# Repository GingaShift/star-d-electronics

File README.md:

# STAR-D Electronics

Electronics repository for the STAR-D (Space Test of Amoeba Response - Dictyostelium) experiment developed within the ESA REXUS/BEXUS programme.

The electronics architecture is divided into several dedicated boards responsible for power conversion, experiment control, imaging, sensing, actuation and illumination.

---

# System Overview

The STAR-D electronics system is organized around:

- Power Board
- Main Control Board
- 5V Distribution Board
- CM5 Imaging System
- Microscope LED Board
- External Sensor Interfaces

---

# Power Board

## Purpose

Interfaces directly with the REXUS Service Module.

Responsibilities:

- 28V input from REXUS
- Power conversion
- Signal isolation
- RS422 communications
- Power distribution to the experiment

## PCB

## Main Components

- DC/DC Converters
- Optocouplers
- RS422 Transceiver
- D-SUB Interface
- Protection circuitry

---

# Main Control Board

## Purpose

Central controller of the experiment.

Responsibilities:

- Sensor acquisition
- Heater control
- Fluidic control
- Experiment sequencing
- Telemetry generation

## PCB

## Main Components

- ESP32-S3
- MAX31865
- PT100 Interface
- LSM6DSM
- ABP Pressure Sensor Interface
- SLF3S Flow Sensor Interface
- Actuator Drivers

---

# 5V Distribution Board

## Purpose

Dedicated power distribution board for high-current 5V subsystems.

Responsibilities:

- CM5 power supply

## PCB

---

# CM5 Imaging System

## Purpose

Scientific image acquisition and storage.

Responsibilities:

- Microscope control
- Camera acquisition
- Data storage
- Image processing

## PCB

## Main Components

- Raspberry Pi CM5
- NVMe SSD
- CSI Camera Interface

---

# Microscope LED PCB

## Purpose

Microscope illumination.

Responsibilities:

- Brightfield illumination
- Fluorescence illumination

## PCB

---

# External BME280 Board

## Purpose

Environmental monitoring outside the Pressure Vessel.

## PCB

---

# Repository Structure

```text
Documentation/
├── SED
├── Part_Listing
├── ICD
└── Images

Power_Board/

Main_Board/

5V_Board/

CM5_System/

Microscope_LED_PCB/

BME280_External/
```

---

# Documentation

Useful documents:

- STAR-D SED
- REXUS ICD
- Global Part Listing
- Power Board Part Listing
- Test Reports
- Integration Documents

---

# Team

STAR-D Electronics Team

Electronic Lead:
**Eden Elfassy**

ESA REXUS/BEXUS Programme

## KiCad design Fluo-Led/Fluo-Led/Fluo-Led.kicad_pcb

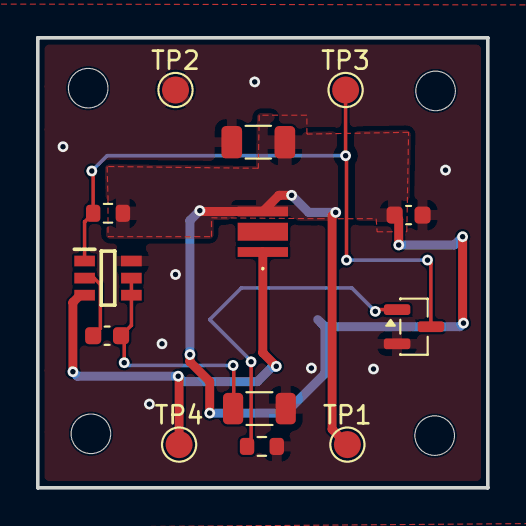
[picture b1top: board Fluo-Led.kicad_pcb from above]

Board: 2 copper layers, 25.0 x 25.0 mm, 18 parts (1 on the bottom side), 7 nets.

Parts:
C1: 100nF 0603; C_0603_1608Metric
C2: 10uF 1206; C_1206_3216Metric
C3: 1 nF 0603; C_0603_1608Metric
H1, H2, H3, H4: MountingHole; MountingHole_2.2mm_M2
IC1: AL5801W6-7; SOT95P285X140-6N
J1: Conn_01x03; Molex_Micro-Fit_3.0_43650-0312_1x03-1MP_P3.00mm_Horizontal
LED1: LV_CRBP.01-KXLY-AD-Q525-350-R18; LVCRBP01KXLYADQ525350R18
Q1: 2N7002; SOT-23
R1: 4.02R 1206; R_1206_3216Metric
R2: 12.4k 0603; R_0603_1608Metric
R3: 100k 0603; R_0603_1608Metric
TP1, TP2, TP3, TP4: TestPoint; TestPoint_Pad_D1.5mm

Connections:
+5V: C1.1, C2.1, J1.1, LED1.2 (A), R2.1, TP1.1 (1_1)
BIAS: IC1.1 (BIAS), Q1.3 (D), R2.2, TP3.1 (1_1)
GND: C1.2, C2.2, IC1.6 (GND), J1.2, Q1.2 (S), R1.2, R3.1, TP2.1 (1_1)
unnamed: C3.1, IC1.4 (REXT), IC1.5 (COMP), R1.1
unnamed: C3.2, IC1.2 (FB)
unnamed: IC1.3 (OUT), LED1.1 (K), TP4.1 (1_1)
PWM_CTRL: J1.3, Q1.1 (G), R3.2

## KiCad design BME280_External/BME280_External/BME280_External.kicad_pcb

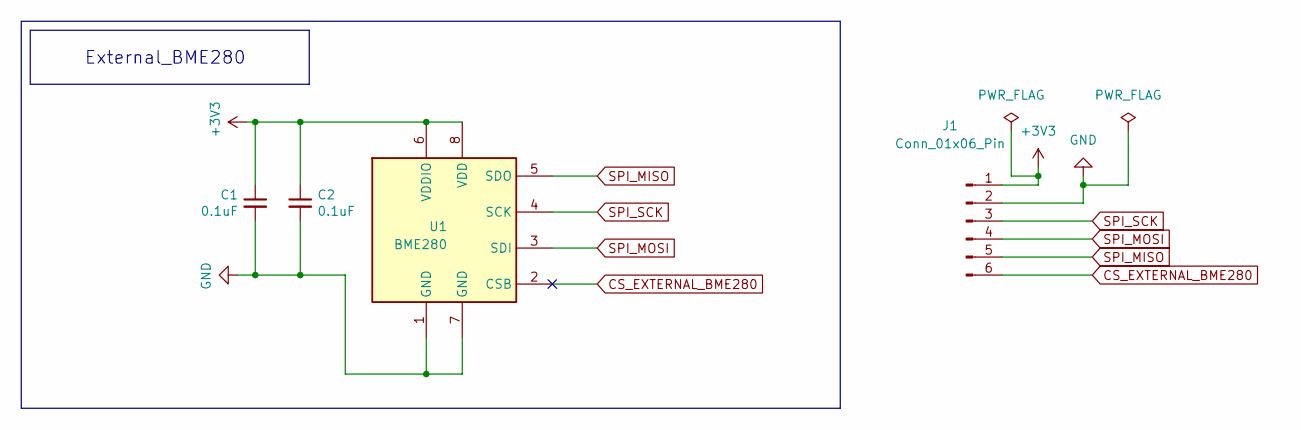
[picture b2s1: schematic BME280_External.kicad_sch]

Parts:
C1, C2: 0.1uF; C_0402_1005Metric
J1: Conn_01x06_Pin; Molex_Micro-Fit_3.0_43650-0615_1x06_P3.00mm_Vertical
U1: BME280; Bosch_LGA-8_2.5x2.5mm_P0.65mm_ClockwisePinNumbering

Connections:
+3V3: C1.1, C2.1, J1.1, U1.6 (VDDIO), U1.8 (VDD)
CS_EXTERNAL_BME280: J1.6, U1.2 (CSB)
GND: C1.2, C2.2, J1.2, U1.1 (GND), U1.7 (GND)
SPI_MISO: J1.5, U1.5 (SDO)
SPI_MOSI: J1.4, U1.3 (SDI)
SPI_SCK: J1.3, U1.4 (SCK)

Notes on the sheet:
External_BME280

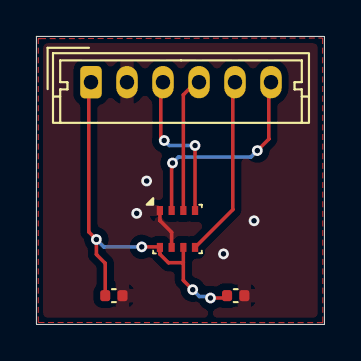
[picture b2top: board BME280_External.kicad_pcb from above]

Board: 2 copper layers, 16.0 x 16.0 mm, 4 parts (0 on the bottom side), 6 nets.

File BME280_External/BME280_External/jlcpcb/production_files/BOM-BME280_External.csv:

Comment,Designator,Footprint,LCSC,Quantity
0.1uF,"C1,C2",C_0402_1005Metric,C141382,2
BME280,U1,Bosch_LGA-8_2.5x2.5mm_P0.65mm_ClockwisePinNumbering,C92489,1
Conn_01x06_Pin,J1,Molex_Micro-Latch_53253-0670_1x06_P2.00mm_Vertical,C564034,1

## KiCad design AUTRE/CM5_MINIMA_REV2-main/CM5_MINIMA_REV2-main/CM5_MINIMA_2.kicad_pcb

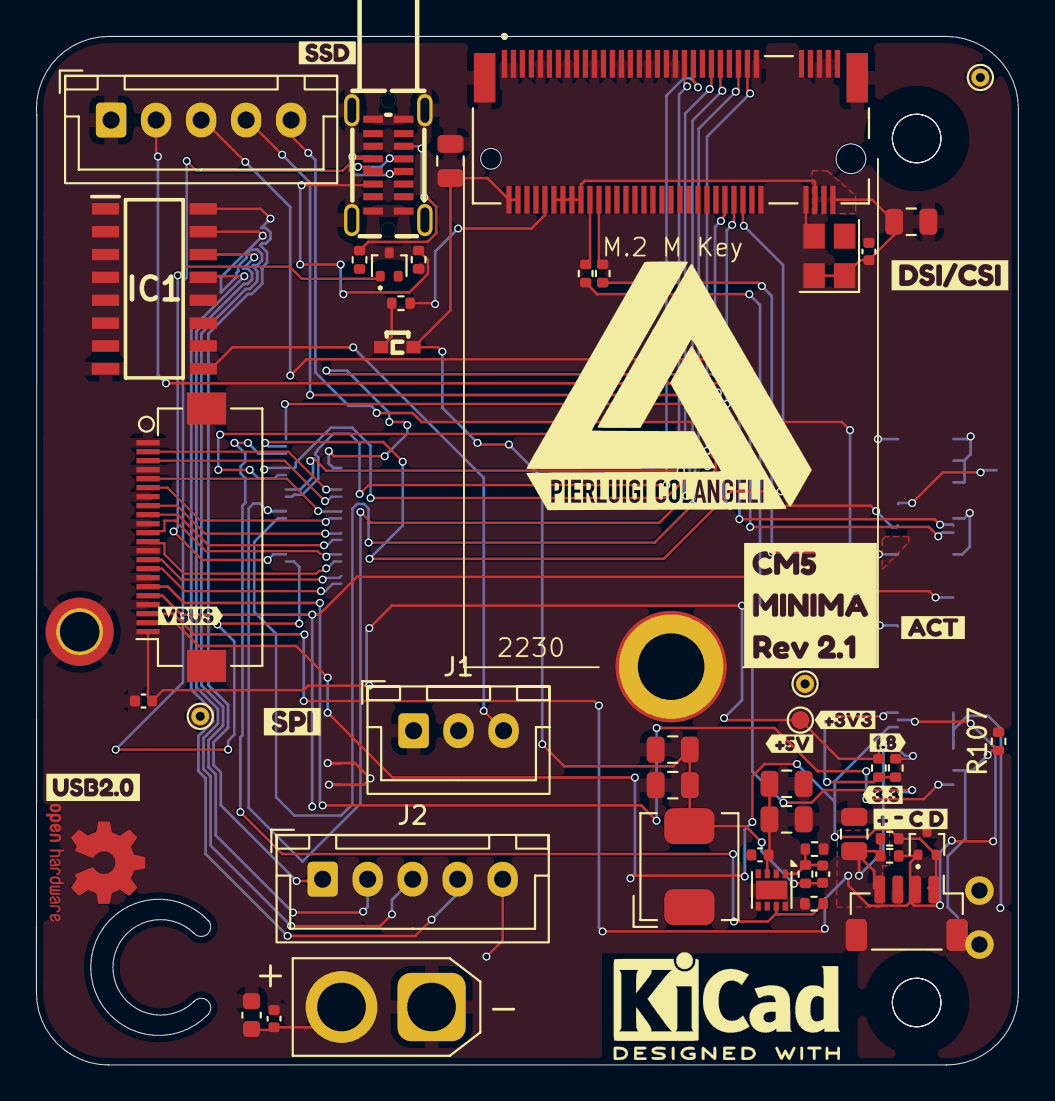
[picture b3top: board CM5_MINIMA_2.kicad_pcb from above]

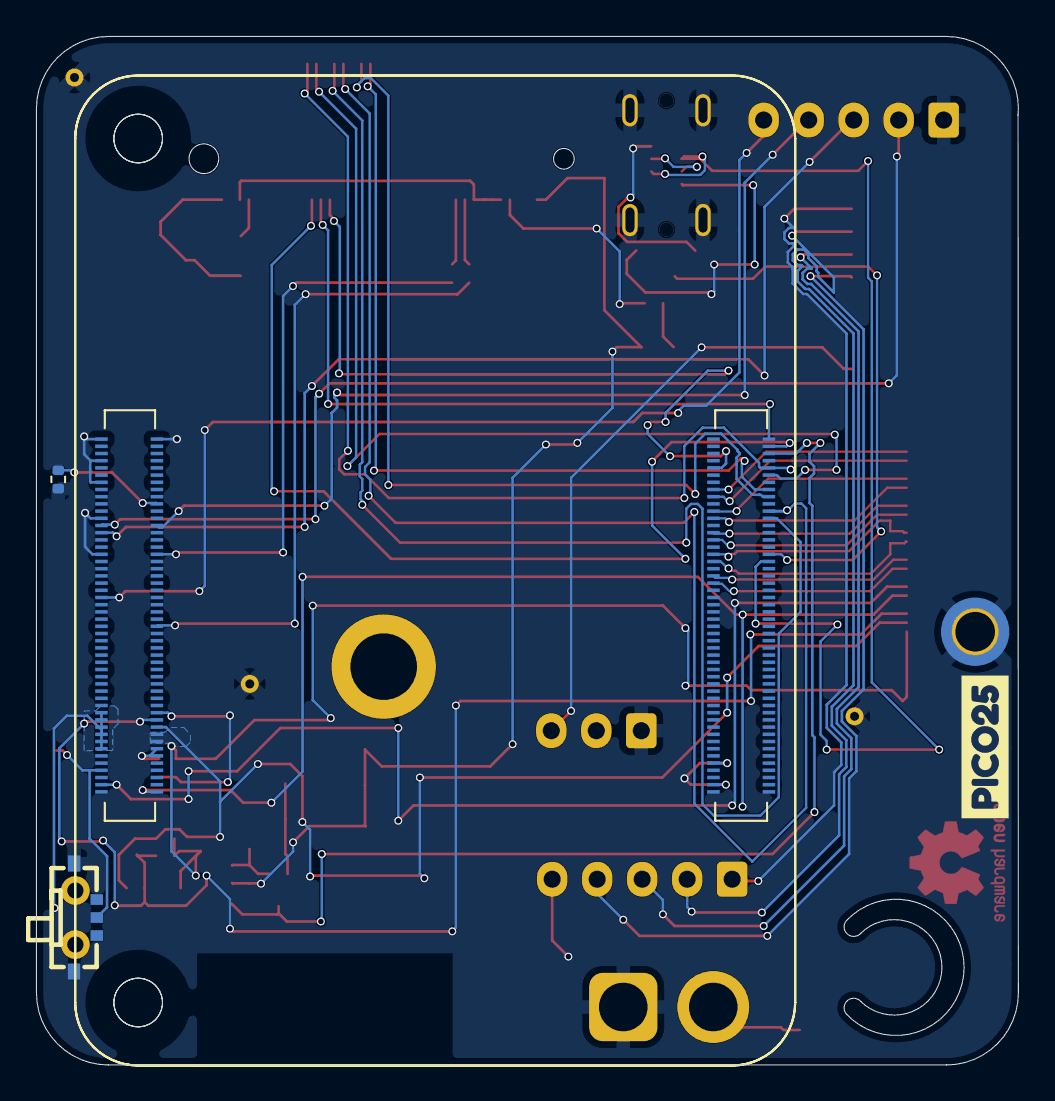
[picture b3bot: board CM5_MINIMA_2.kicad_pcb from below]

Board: 4 copper layers, 54.6 x 57.1 mm, 64 parts (5 on the bottom side), 58 nets.

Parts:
C31: 10uF 0603; C_0603_1608Metric
C33: 100nF 0402; C_0402_1005Metric
C601: 4u7; C_0805_2012Metric
C602, C706, C712: 100n; C_0402_1005Metric
C704, C705, C708, C709, C710, C711: 10u; C_0805_2012Metric
C707: 4.7nF; C_0402_1005Metric
D502, D701: RCLAMP0502BA; SOT-416
D702: GREEN; LED-SMD_L1.7-W0.6-RD
H101: MountingHole_Pad; MountingHole_2.2mm_M2_DIN965_Pad_TopBottom
IC1: ULN2003ADR; SOIC127P600X175-16N
J1: Conn_01x03; JST_XH_B3B-XH-A_1x03_P2.50mm_Vertical
J2, J3: Conn_01x05; JST_XH_B5B-XH-A_1x05_P2.50mm_Vertical
J13: Conn_01x02_Pin; AMASS_XT30U-F_1x02_P5.0mm_Vertical
J502: I2C; JST_SH_BM04B-SRSS-TB_1x04-1MP_P1.00mm_Vertical
J701: Bus_M.2_Socket_M; M.2 M Key socket 2230
J802: Conn_01x22_Female; Hirose_FH12-22S-0.5SH_1x22-1MP_P0.50mm_Horizontal
L701: 2.2uH; L_Bourns_SRP5030CC
M701: M.2 Solder Nut; MountingHole_3.78mm_M2_Pad_TopOnly
Module301: ComputeModule5-CM5; Raspberry-Pi-5-Compute-Module_GPIO
Module302: ComputeModule5-CM5; Raspberry-Pi-5-Compute-Module_HSS
R102, R103, R105, R106: 0R; R_0402_1005Metric
R104, R107, R705: 10k; R_0402_1005Metric
R501, R502, R706, R707: 2k2; R_0402_1005Metric
R702, R703: 5.1k; R_0402_1005Metric
R704: 100k; R_0402_1005Metric
SW101: MK-11C04-G013; SW-SMD_MK-11C04-G013
TP103: +3V3_PI; TestPoint_Pad_D1.0mm
TP104, TP105, TP106: GND; TestPoint_THTPad_D1.0mm_Drill0.5mm
U702: AP3441SHE-7B; DFN-8-1EP_2x2mm_P0.5mm_EP1.05x1.75mm
U703: ASEK-32.768KHZ-L-R-T; Crystal_SMD_3225-4Pin_3.2x2.5mm
USB701: TYPEC-305-ACP16H458; USB-C-SMD_TYPEC-305-ACP16H458
kibuzzard-675EDCA4: G***; kibuzzard-675EDCA4
kibuzzard-679BB153: G***; kibuzzard-679BB153
kibuzzard-6772DA33: G***; kibuzzard-6772DA33
kibuzzard-6773B9B9: G***; kibuzzard-6773B9B9
kibuzzard-6773B9CA: G***; kibuzzard-6773B9CA
kibuzzard-6773BA43: G***; kibuzzard-6773BA43
kibuzzard-6773BA89: G***; kibuzzard-6773BA89
kibuzzard-6773C2D7: G***; kibuzzard-6773C2D7
kibuzzard-6773C222: G***; kibuzzard-6773C222
kibuzzard-6773C376: G***; kibuzzard-6773C376
kibuzzard-6773CC4D: G***; kibuzzard-6773CC4D
kibuzzard-6773CC39: G***; kibuzzard-6773CC39
kibuzzard-67758943: G***; kibuzzard-67758943

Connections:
+1V8: Module301.88 (+1.8v_(Output)), Module301.90 (+1.8v_(Output)), R103.1
+3V3_PI: C601.1, C602.1, J502.4, J802.22, Module301.84 (+3.3v_(Output)), Module301.86 (+3.3v_(Output)), R102.1, R501.1, R502.1, TP103.1 (1_1)
+5V: C704.1, C705.1, C706.1, U702.3 (VIN)
+5V_MAIN: C31.1, C33.1, IC1.9 (COM), J1.3, J2.5, J13.2, Module301.77 (+5v_(Input)), Module301.79 (+5v_(Input)), Module301.81 (+5v_(Input)), Module301.83 (+5v_(Input)), Module301.85 (+5v_(Input)), Module301.87 (+5v_(Input))
/CM5/CAM_GPIO0: J802.17, Module301.97 (CAM_GPIO0)
/CM5/CAM_GPIO1: J802.18, Module301.100 (CAM_GPIO1)
/CM5/DPHY0_P.C_N: J802.8, Module302.127 (MIPI0_C_N)
/CM5/DPHY0_P.C_P: J802.9, Module302.129 (MIPI0_C_P)
/CM5/DPHY0_P.D0_N: J802.2, Module302.115 (MIPI0_D0_N)
/CM5/DPHY0_P.D0_P: J802.3, Module302.117 (MIPI0_D0_P)
/CM5/DPHY0_P.D1_N: J802.5, Module302.121 (MIPI0_D1_N)
/CM5/DPHY0_P.D1_P: J802.6, Module302.123 (MIPI0_D1_P)
/CM5/DPHY0_P.D2_N: J802.11, Module302.133 (MIPI0_D2_N)
/CM5/DPHY0_P.D2_P: J802.12, Module302.135 (MIPI0_D2_P)
/CM5/DPHY0_P.D3_N: J802.14, Module302.139 (MIPI0_D3_N)
/CM5/DPHY0_P.D3_P: J802.15, Module302.141 (MIPI0_D3_P)
/CM5/EEPROM_nWP: Module301.20 (EEPROM_nWP), R104.2
/CM5/GPIO4: Module301.54 (GPIO4), R106.2
/CM5/GPIO5: Module301.34 (GPIO5), R105.2
/CM5/GPIO_VREF: Module301.78 (GPIO_VREF(1.8v/3.3v_Input)), R102.2, R103.2
/CM5/PCIE_PI.CLK_N: J701.53 (REFCLKn), Module302.112 (PCIe_CLK_N)
/CM5/PCIE_PI.CLK_P: J701.55 (REFCLKp), Module302.110 (PCIe_CLK_P)
/CM5/PCIE_PI.PWR_EN: Module302.106 (PCIE_PWR_EN), R704.1, U702.7 (EN)
/CM5/PCIE_PI.RX_N: J701.43 (PETp0), Module302.118 (PCIe_RX_N)
/CM5/PCIE_PI.RX_P: J701.41 (PETn0), Module302.116 (PCIe_RX_P)
/CM5/PCIE_PI.TX_N: J701.49 (PERp0), Module302.124 (PCIe_TX_N)
/CM5/PCIE_PI.TX_P: J701.47 (PERn0), Module302.122 (PCIe_TX_P)
/CM5/PCIE_PI.nCLKREQ: J701.52 (~CLKREQ), Module302.102 (PCIe_nCLKREQ)
/CM5/PCIE_PI.nRST: J701.50 (~PERST), Module302.109 (PCIe_nRST)
/CM5/PCIE_PI.nWAKE: J701.54 (~PEWAKE), Module302.104 (PCIE_nWAKE)
/CM5/USB2P.D_N: D701.2 (K2), Module302.136 (USB3-0-D_N), USB701.A7 (D-), USB701.B7 (D-)
/CM5/USB2P.D_P: D701.1 (K1), Module302.134 (USB3-0-D_P), USB701.A6 (D+), USB701.B6 (D+)
/CM5/nRPIBOOT: Module301.93 (nRPIBOOT), R107.1, SW101.C
/IO/COIL_A: IC1.16 (1C), J2.1
/IO/COIL_B: IC1.15 (2C), J2.2
/IO/COIL_C: IC1.14 (3C), J2.3
/IO/COIL_D: IC1.13 (4C), J2.4
/PCIe-M2/FB: C707.2, R705.2, R706.1, U702.1 (FB)
/PCIe-M2/RX: J701.22 (NC), R105.1
/PCIe-M2/TX: J701.20 (NC), R106.1
/SCL: D502.1 (K1), J502.2, J802.20, Module301.80 (SCL0), R502.2
/SDA: D502.2 (K2), J502.1, J802.21, Module301.82 (SDA0), R501.2
/USB/CC1: R703.1, USB701.A5 (CC1)
/USB/CC2: R702.1, USB701.B5 (CC2)
CS_RASP: J3.5, Module301.45 (GPIO24)
GND: C31.2, C33.2, C601.2, C602.2, C704.2, C705.2, C706.2, C708.2, C709.2, C710.2, C711.2, C712.2, D502.3 (A), D701.3 (A), H101.1 (1_1), IC1.8 (E), J1.1, J3.1, J13.1, J502.3, J701.1 (GND), J701.3 (GND), J701.9 (GND), J701.15 (GND), J701.21 (GND), J701.27 (GND), J701.33 (GND), J701.39 (GND), J701.45 (GND), J701.51 (GND), J701.57 (GND), J701.71 (GND), J701.73 (GND), J701.75 (GND), J701.S1, J701.S2, J802.1, J802.4, J802.7, J802.10, J802.13, J802.16, J802.19, Module301.1 (GND), Module301.2 (GND), Module301.7 (GND), Module301.8 (GND), Module301.13 (GND), Module301.14 (GND), Module301.22 (GND), Module301.23 (GND), Module301.32 (GND), Module301.33 (GND), Module301.42 (GND), Module301.43 (GND), Module301.52 (GND), Module301.53 (GND), Module301.59 (GND), Module301.60 (GND), Module301.65 (GND), Module301.66 (GND), Module301.71 (GND), Module301.74 (GND), Module301.98 (GND), Module302.107 (GND), Module302.108 (GND), Module302.113 (GND), Module302.114 (GND), Module302.119 (GND), Module302.120 (GND), Module302.125 (GND), Module302.126 (GND), Module302.131 (GND), Module302.132 (GND), Module302.137 (GND), Module302.138 (GND), Module302.144 (GND), Module302.150 (GND), Module302.155 (GND), Module302.156 (GND), Module302.161 (GND), Module302.162 (GND), Module302.167 (GND), Module302.168 (GND), Module302.173 (GND), Module302.174 (GND), Module302.179 (GND), Module302.180 (GND), Module302.185 (GND), Module302.186 (GND), Module302.191 (GND), Module302.192 (GND), Module302.197 (GND), Module302.198 (GND), R104.1, R702.2, R703.2, R704.2, R706.2, SW101.5, TP104.1 (1_1), TP105.1 (1_1), TP106.1 (1_1), U702.4 (PGND), U702.8 (SGND), U702.9 (PAD), U703.2 (GND), USB701.1 (EP), USB701.A1 (GND), USB701.A12 (GND), USB701.B1 (GND), USB701.B12 (GND)
M2_3V3: C707.1, C708.1, C709.1, C710.1, C711.1, C712.1, D702.2 (A), J701.2 (3.3V), J701.4 (3.3V), J701.12 (3.3V), J701.14 (3.3V), J701.16 (3.3V), J701.18 (3.3V), J701.70 (3.3V), J701.72 (3.3V), J701.74 (3.3V), L701.2, R705.1, U703.1 (EN), U703.4 (VDD)
unnamed: D702.1 (K), R707.1
unnamed: J701.10 (DAS/~DSS/~LED1), R707.2
unnamed: J701.68 (SUSCLK), U703.3 (Out)
unnamed: L701.1, U702.6 (LX)
RASP_CLK: J3.2, Module301.25 (GPIO21)
RASP_MISO: J3.4, Module301.26 (GPIO19)
RASP_MOSI: J3.3, Module301.27 (GPIO20)
STEP_IN1: IC1.1 (1B), Module301.29 (GPIO16)
STEP_IN2: IC1.2 (2B), Module301.31 (GPIO12)
STEP_IN3: IC1.3 (3B), Module301.37 (GPIO7)
STEP_IN4: IC1.4 (4B), Module301.39 (GPIO8)

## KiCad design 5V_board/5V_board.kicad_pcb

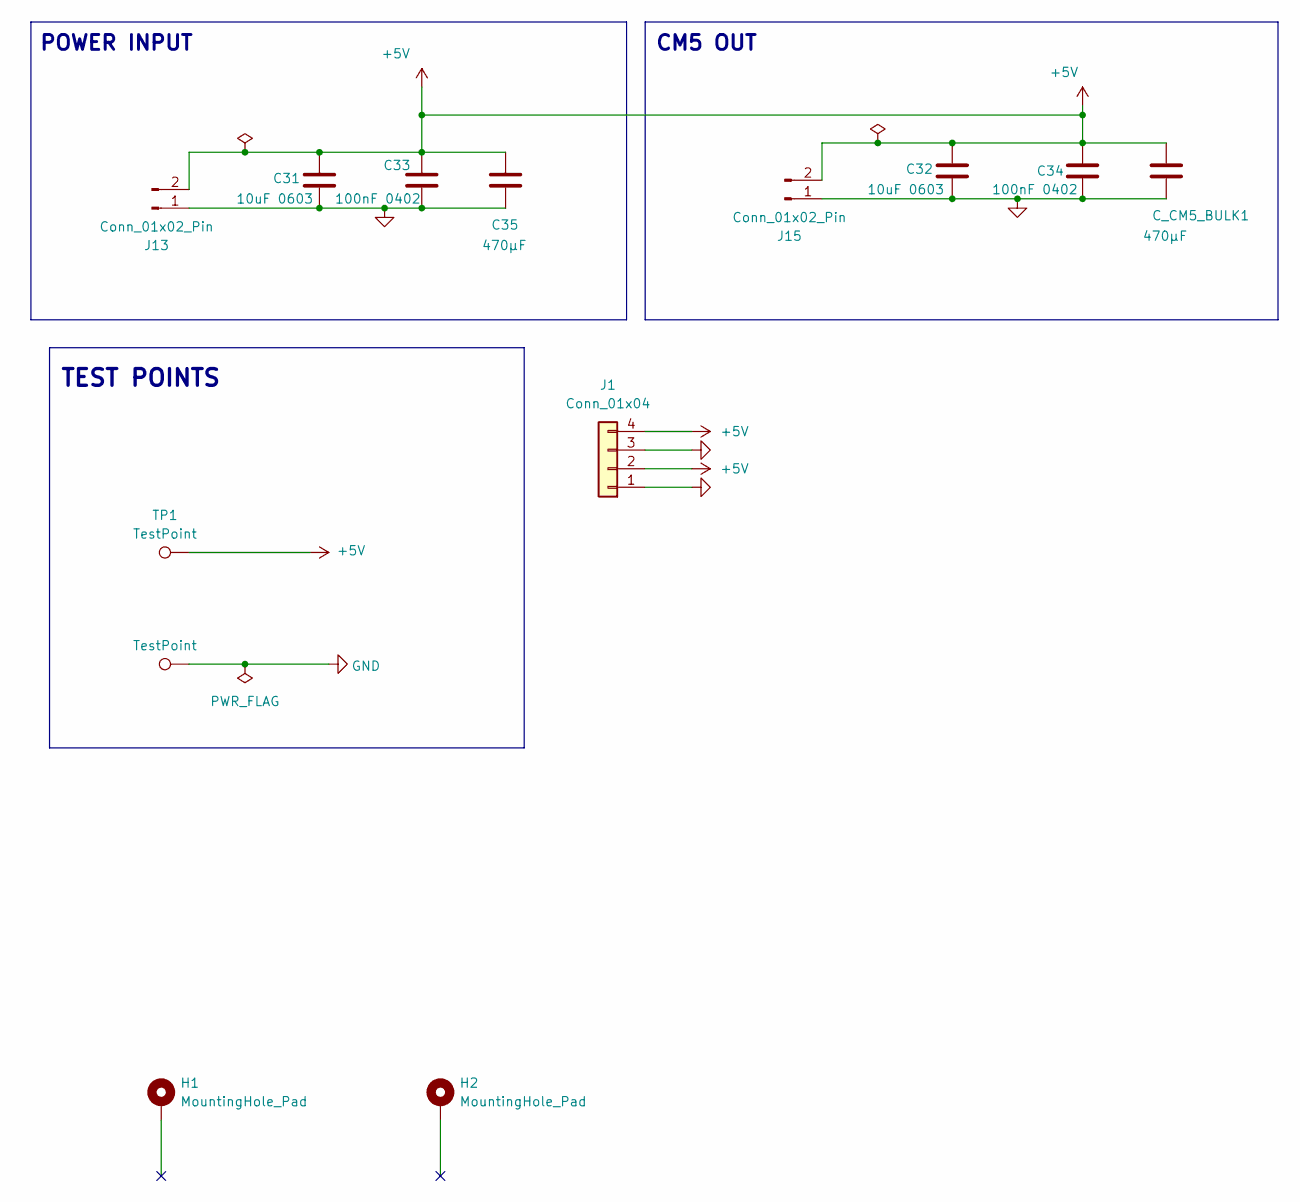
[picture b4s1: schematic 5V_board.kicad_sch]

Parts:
C31, C32: 10uF 0603; C_0603_1608Metric
C33, C34: 100nF 0402; C_0402_1005Metric
C35: 470µF; CP_Elec_6.3x7.7
C_CM5_BULK1: 470µF; CP_Elec_6.3x7.7
H1, H2: MountingHole_Pad; MountingHole_3.2mm_M3_Pad
J1: Conn_01x04; Molex_Micro-Latch_53253-0470_1x04_P2.00mm_Vertical
J13, J15: Conn_01x02_Pin; Molex_Micro-Fit_3.0_43650-0215_1x02_P3.00mm_Vertical
TP1, TP3: TestPoint; TestPoint_Pad_D1.5mm

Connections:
+5V: C31.1, C32.1, C33.1, C34.1, C35.1, C_CM5_BULK1.1, J1.2, J1.4, J13.2, J15.2, TP1.1 (1_1)
GND: C31.2, C32.2, C33.2, C34.2, C35.2, C_CM5_BULK1.2, J1.1, J1.3, J13.1, J15.1, TP3.1 (1_1)

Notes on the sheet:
TEST POINTS
POWER INPUT
CM5 OUT

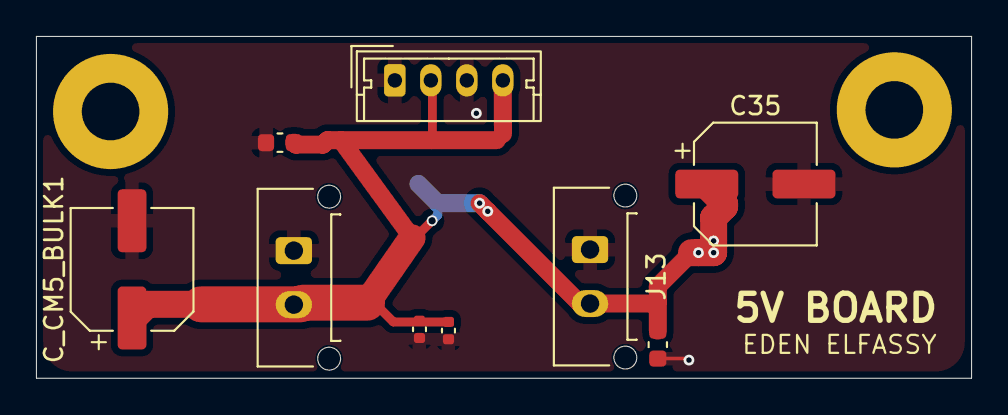
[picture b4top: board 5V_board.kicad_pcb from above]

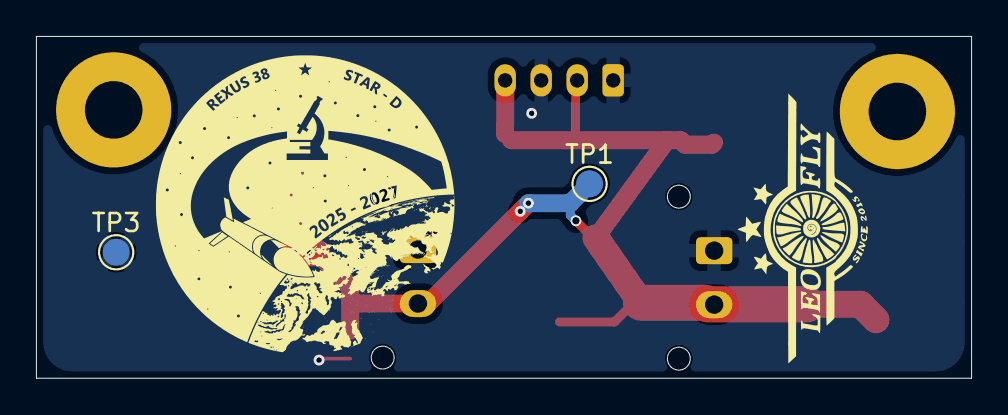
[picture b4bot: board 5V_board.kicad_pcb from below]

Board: 2 copper layers, 51.9 x 19.0 mm, 13 parts (2 on the bottom side), 2 nets.

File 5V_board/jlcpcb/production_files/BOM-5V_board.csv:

Comment,Designator,Footprint,LCSC,Quantity
100nF 0402,"C33,C34",C_0402_1005Metric,C307331,2
10uF 0603,"C31,C32",C_0603_1608Metric,C96446,2
470µF,"C35,C_CM5_BULK1",CP_Elec_6.3x7.7,C3354,2
Conn_01x02_Pin,"J13,J15",Molex_Micro-Fit_3.0_43650-0215_1x02_P3.00mm_Vertical,C293740,2
Conn_01x04,J1,Molex_Micro-Latch_53253-0470_1x04_P2.00mm_Vertical,C504808,1

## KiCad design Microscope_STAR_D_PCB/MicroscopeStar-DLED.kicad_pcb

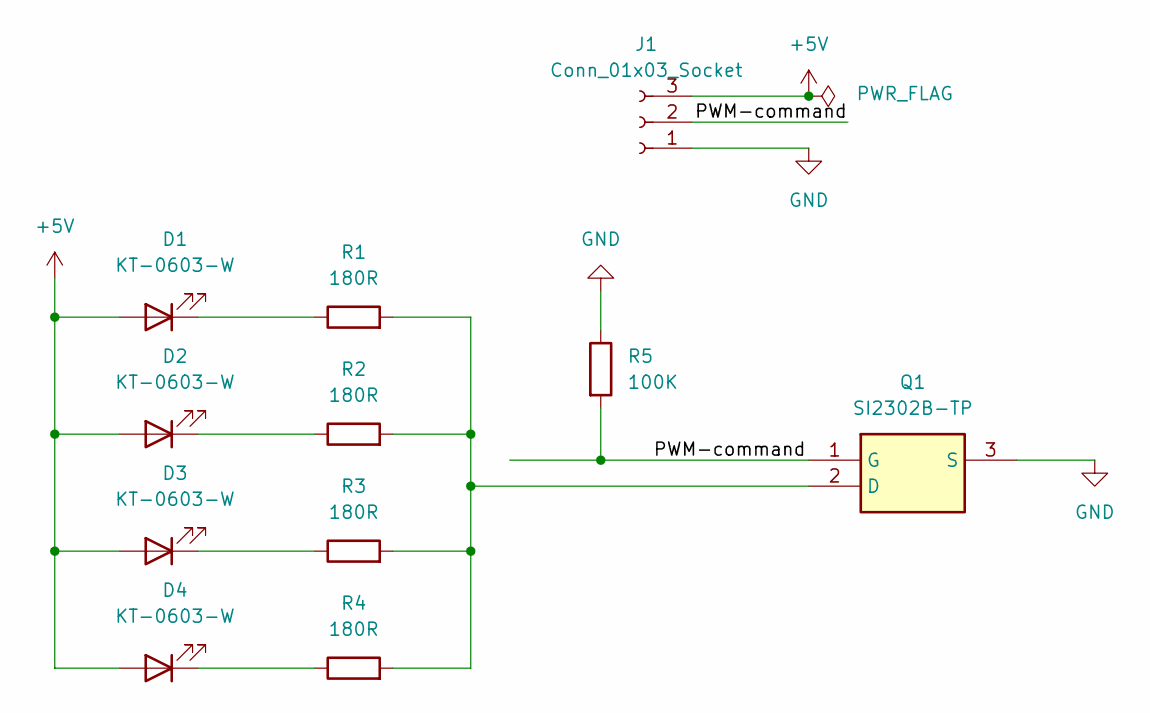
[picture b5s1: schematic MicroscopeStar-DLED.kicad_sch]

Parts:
D1, D2, D3, D4: KT-0603-W; LED_0603_1608Metric
J1: Conn_01x03_Socket; Molex_Micro-Fit_3.0_43650-0312_1x03-1MP_P3.00mm_Horizontal
Q1: SI2302B-TP; SOT95P237X125-3N; Manufacturer_Part_Number SI2302B-TP; Mouser Part Number 833-SI2302B-TP
R1, R2, R3, R4: 180R; R_0402_1005Metric
R5: 100K

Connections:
+5V: D1.2 (A), D2.2 (A), D3.2 (A), D4.2 (A), J1.3
/PWM-command: J1.2, Q1.1 (G), R5.2
GND: J1.1, Q1.3 (S), R5.1
unnamed: D1.1 (K), R1.1
unnamed: D2.1 (K), R2.1
unnamed: D3.1 (K), R3.1
unnamed: D4.1 (K), R4.1
unnamed: Q1.2 (D), R1.2, R2.2, R3.2, R4.2

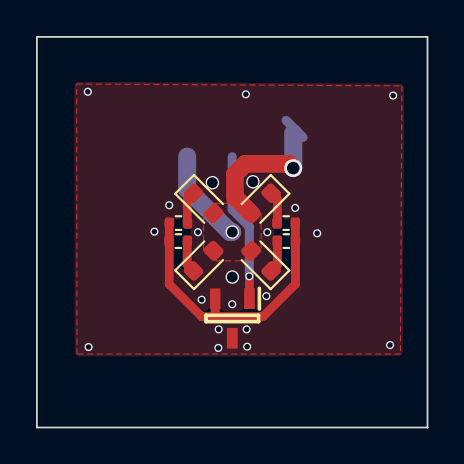
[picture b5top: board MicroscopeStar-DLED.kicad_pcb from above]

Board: 2 copper layers, 21.7 x 21.7 mm, 10 parts (1 on the bottom side), 8 nets.

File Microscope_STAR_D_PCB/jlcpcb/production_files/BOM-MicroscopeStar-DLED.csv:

Comment,Designator,Footprint,LCSC,Quantity
180R,"R1,R2,R3,R4",R_0402_1005Metric,C138045,4
Conn_01x03_Socket,J1,Molex_Micro-Fit_3.0_43650-0312_1x03-1MP_P3.00mm_Horizontal,C114109,1
KT-0603-W,"D1,D2,D3,D4",LED_0603_1608Metric,C5973179,4
SI2302B-TP,Q1,SOT95P237X125-3N,C52117627,1

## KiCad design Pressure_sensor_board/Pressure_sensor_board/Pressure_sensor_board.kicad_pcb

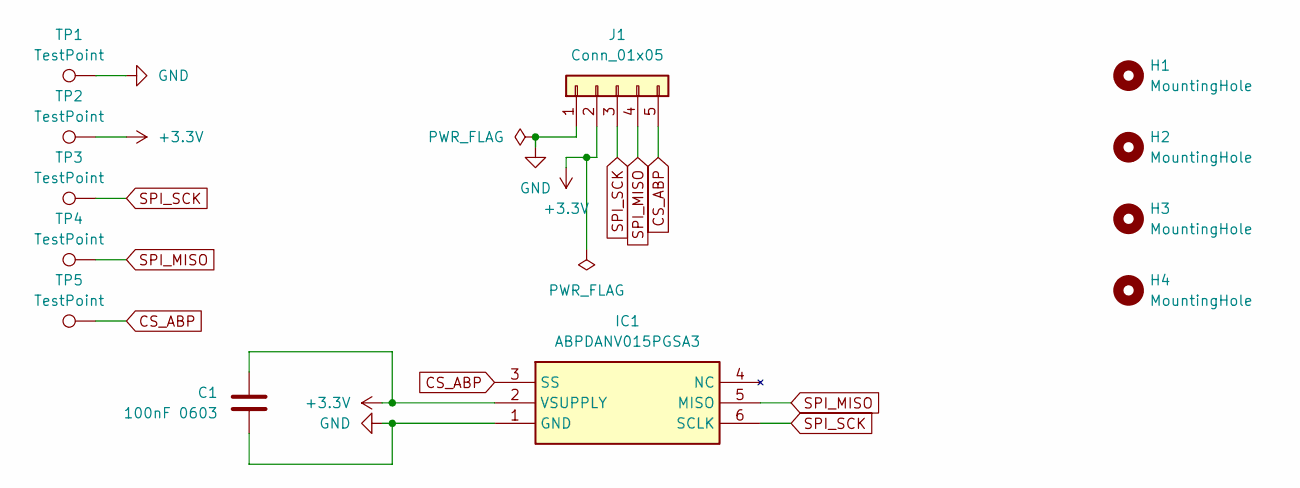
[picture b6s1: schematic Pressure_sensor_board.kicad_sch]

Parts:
C1: 100nF 0603; C_0603_1608Metric
H1, H2, H3, H4: MountingHole; MountingHole_2.2mm_M2
IC1: ABPDANV015PGSA3; Manufacturer_Part_Number ABPDANV015PGSA3; Mouser Part Number 785-ABPDANV015PGSA3
J1: Conn_01x05; Molex_Micro-Latch_53254-0570_1x05_P2.00mm_Horizontal
TP1, TP2, TP3, TP4, TP5: TestPoint; TestPoint_Pad_D1.5mm

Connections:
+3.3V: C1.2, IC1.2 (VSUPPLY), J1.2, TP2.1 (1_1)
CS_ABP: IC1.3 (SS), J1.5, TP5.1 (1_1)
GND: C1.1, IC1.1 (GND), J1.1, TP1.1 (1_1)
SPI_MISO: IC1.5 (MISO), J1.4, TP4.1 (1_1)
SPI_SCK: IC1.6 (SCLK), J1.3, TP3.1 (1_1)

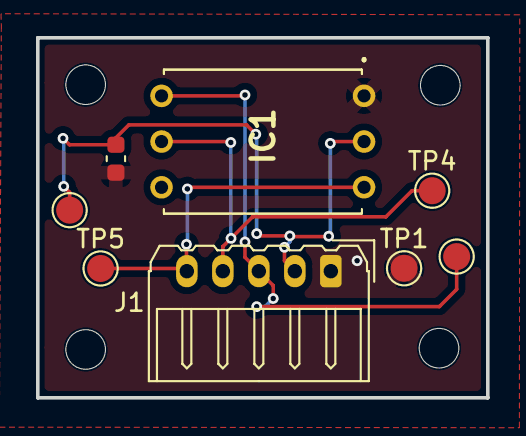
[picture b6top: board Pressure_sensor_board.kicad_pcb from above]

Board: 2 copper layers, 25.0 x 20.0 mm, 12 parts (0 on the bottom side), 5 nets.

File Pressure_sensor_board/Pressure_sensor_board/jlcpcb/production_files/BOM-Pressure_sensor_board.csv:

Comment,Designator,Footprint,LCSC,Quantity
100nF 0603,C1,C_0603_1608Metric,C24452,1
Conn_01x05,J1,Molex_Micro-Latch_53254-0570_1x05_P2.00mm_Horizontal,C585950,1
ABPDANV015PGSA3,IC1,ABPDANV015PGSA3,,1

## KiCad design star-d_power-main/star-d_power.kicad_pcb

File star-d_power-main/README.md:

# star-d_power
STAR-D power PCB

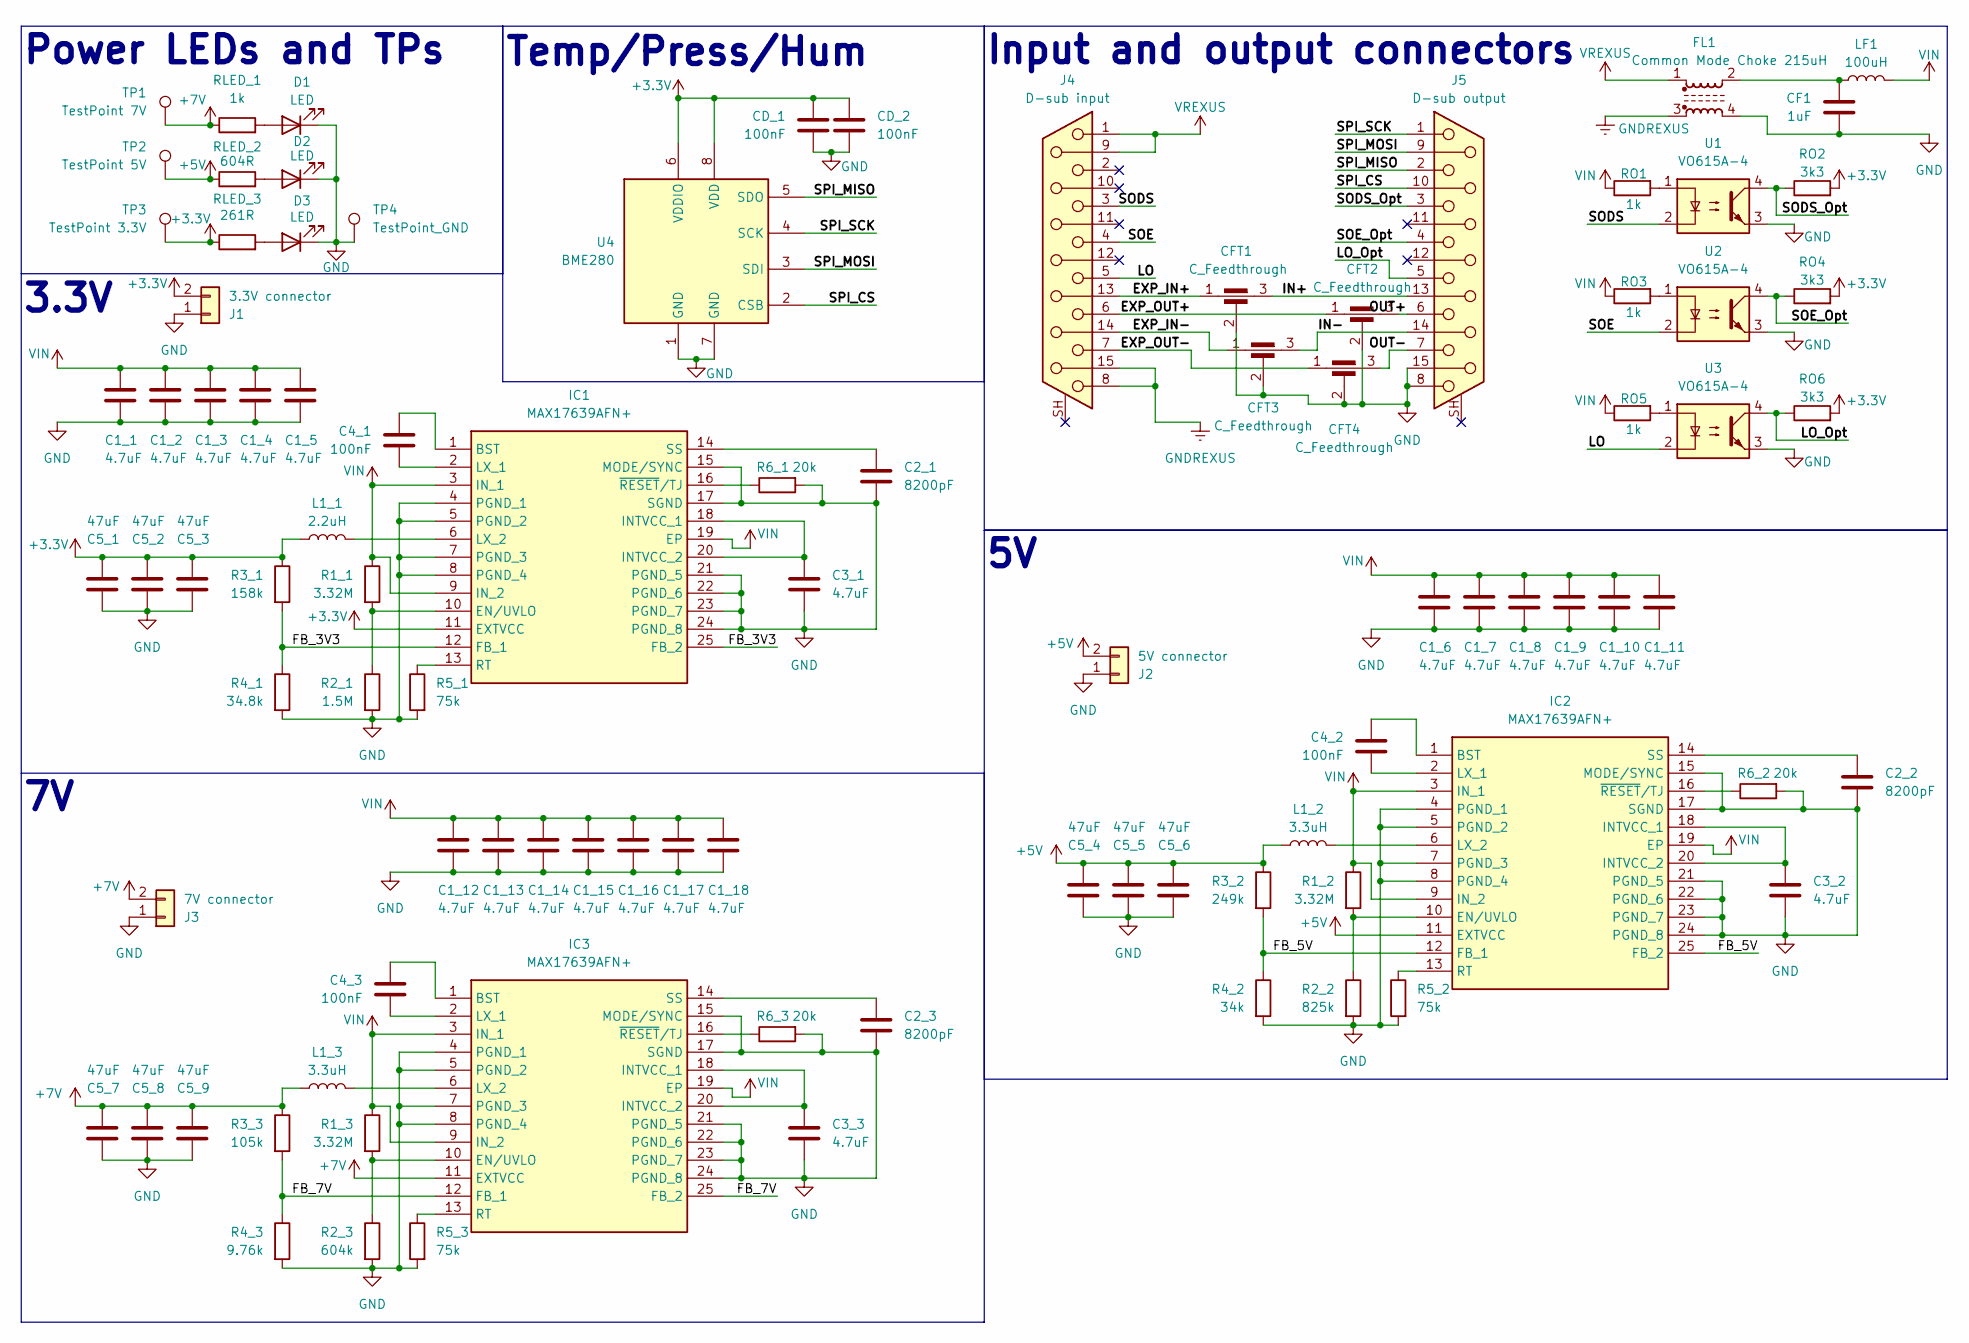
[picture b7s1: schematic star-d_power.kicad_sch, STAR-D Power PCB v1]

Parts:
C1_1, C1_2, C1_3, C1_4, C1_5, C1_6, C1_7, C1_8, C1_9, C1_10, C1_11, C1_12, C1_13, C1_14, C1_15, C1_16, C1_17, C1_18: 4.7uF; C_1206_3216Metric; Manufacturer_Part_Number GRM31CR71H475KA12L
C2_1, C2_2, C2_3: 8200pF; C_0603_1608Metric; Manufacturer_Part_Number VJ0603Y822KXAAC
C3_1, C3_2, C3_3: 4.7uF; C_0603_1608Metric; Manufacturer_Part_Number GRM188Z71A475ME15D
C4_1, C4_2, C4_3: 100nF; C_0603_1608Metric; Manufacturer_Part_Number C0603C104K3RAC7411
C5_1, C5_2, C5_3, C5_4, C5_5, C5_6: 47uF; C_1210_3225Metric; Manufacturer_Part_Number GRM32ER71A476KE15L
C5_7, C5_8, C5_9: 47uF; C_2220_5750Metric; Manufacturer_Part_Number CGA9N3X7R1E476M230KB
CD_1, CD_2: 100nF; C_0603_1608Metric; Manufacturer_Part_Number C0603C104K3RAC7411
CF1: 1uF; C_1206_3216Metric; Manufacturer_Part_Number C3216X7R1H105K160AB
CFT1, CFT2, CFT3, CFT4: C_Feedthrough; NFM18CC101R1C3D; Manufacturer_Part_Number NFM18CC221R1C3D
D1, D2, D3: LED; LED_0603_1608Metric; Manufacturer_Part_Number LTST-C191KFKT
FL1: Common Mode Choke 215uH; PA2754NL; Manufacturer_Part_Number PA2754NL
IC1, IC2, IC3: MAX17639AFN+; MAX17793AFN; Manufacturer_Part_Number MAX17639AFN+
J1: 3.3V connector; Molex_Micro-Fit_3.0_43650-0200_1x02_P3.00mm_Horizontal; Manufacturer_Part_Number 43650-0200
J2: 5V connector; Molex_Micro-Fit_3.0_43650-0200_1x02_P3.00mm_Horizontal; Manufacturer_Part_Number 43650-0200
J3: 7V connector; Molex_Micro-Fit_3.0_43650-0200_1x02_P3.00mm_Horizontal; Manufacturer_Part_Number 43650-0200
J4: D-sub input; AMPHENOL_LD15P33E4GX00LF; Manufacturer_Part_Number LD15P33E4GX00LF
J5: D-sub output; AMPHENOL_LD15S33E4GV00LF; Manufacturer_Part_Number LD15S33E4GV00LF
L1_1: 2.2uH; IND_XGL1010-222MED; Manufacturer_Part_Number XGL1010-222MED
L1_2, L1_3: 3.3uH; IND_XGL1010-222MED; Manufacturer_Part_Number XGL1010-332MED
LF1: 100uH; INDPM235220X1300N; Manufacturer_Part_Number SRP2313AA-101M
R1_1, R1_2, R1_3: 3.32M; R_0603_1608Metric; Manufacturer_Part_Number CRCW06033M32FKEA
R2_1: 1.5M; R_0603_1608Metric; Manufacturer_Part_Number CRCW06031M50FKEA
R2_2: 825k; R_0603_1608Metric; Manufacturer_Part_Number CRCW0603825KFKEA
R2_3: 604k; R_0603_1608Metric; Manufacturer_Part_Number CRCW0603604KFKEA
R3_1: 158k; R_0603_1608Metric; Manufacturer_Part_Number CRCW0603158KFKEA
R3_2: 249k; R_0603_1608Metric; Manufacturer_Part_Number CRCW0603249KFKEA
R3_3: 105k; R_0603_1608Metric; Manufacturer_Part_Number CRCW0603105KFKEA
R4_1: 34.8k; R_0603_1608Metric; Manufacturer_Part_Number CRCW060334K8FKEA
R4_2: 34k; R_0603_1608Metric; Manufacturer_Part_Number CRCW060334K0FKEA
R4_3: 9.76k; R_0603_1608Metric; Manufacturer_Part_Number CRCW06039K76FKEA
R5_1, R5_2, R5_3: 75k; R_0603_1608Metric; Manufacturer_Part_Number CRCW060375K0FKEA
R6_1, R6_2, R6_3: 20k; R_0603_1608Metric; Manufacturer_Part_Number CRCW060320K0FKEA
RLED_1: 1k; R_0603_1608Metric; Manufacturer_Part_Number ERJ-PA3J102V
RLED_2: 604R; R_0603_1608Metric; Manufacturer_Part_Number ERJ-PA3D6040V
RLED_3: 261R; R_0603_1608Metric; Manufacturer_Part_Number ERJ-PA3F2610V
RO1, RO3, RO5: 1k; R_0603_1608Metric; Manufacturer_Part_Number ERJ-PA3J102V
RO2, RO4, RO6: 3k3; R_0603_1608Metric; Manufacturer_Part_Number ERJ-PA3J332V
TP1: TestPoint 7V; TestPoint_Pad_D1.0mm
TP2: TestPoint 5V; TestPoint_Pad_D1.0mm
TP3: TestPoint 3.3V; TestPoint_Pad_D1.0mm
TP4: TestPoint_GND; TestPoint_Plated_Hole_D3.0mm
U1, U2, U3: VO615A-4; DIP-4_W10.16mm; Manufacturer_Part_Number VO615A-4
U4: BME280; Bosch_LGA-8_2.5x2.5mm_P0.65mm_ClockwisePinNumbering; Manufacturer_Part_Number BME280

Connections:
+3.3V: C5_1.2, C5_2.2, C5_3.2, CD_1.1, CD_2.1, IC1.11 (EXTVCC), J1.2, L1_1.2, R3_1.1, RLED_3.1, RO2.2, RO4.2, RO6.2, TP3.1 (1_1), U4.6 (VDDIO), U4.8 (VDD)
+5V: C5_4.2, C5_5.2, C5_6.2, IC2.11 (EXTVCC), J2.2, L1_2.2, R3_2.1, RLED_2.1, TP2.1 (1_1)
+7V: C5_7.2, C5_8.2, C5_9.2, IC3.11 (EXTVCC), J3.2, L1_3.2, R3_3.1, RLED_1.1, TP1.1 (1_1)
/EXP_IN+: CFT1.1, J4.13
/EXP_IN-: CFT3.1, J4.14
/EXP_OUT+: CFT2.1, J4.6
/EXP_OUT-: CFT4.1, J4.7
/FB_3V3: IC1.12 (FB_1), IC1.25 (FB_2), R3_1.2, R4_1.1
/FB_5V: IC2.12 (FB_1), IC2.25 (FB_2), R3_2.2, R4_2.1
/FB_7V: IC3.12 (FB_1), IC3.25 (FB_2), R3_3.2, R4_3.1
/IN+: CFT1.3, J5.13
/IN-: CFT3.3, J5.14
/LO: J4.5, U3.2
/LO_Opt: J5.5, RO6.1, U3.4
/OUT+: CFT2.3, J5.6
/OUT-: CFT4.3, J5.7
/SODS: J4.3, U1.2
/SODS_Opt: J5.3, RO2.1, U1.4
/SOE: J4.4, U2.2
/SOE_Opt: J5.4, RO4.1, U2.4
/SPI_CS: J5.10, U4.2 (CSB)
/SPI_MISO: J5.2, U4.5 (SDO)
/SPI_MOSI: J5.9, U4.3 (SDI)
/SPI_SCK: J5.1, U4.4 (SCK)
GND: C1_1.2, C1_2.2, C1_3.2, C1_4.2, C1_5.2, C1_6.2, C1_7.2, C1_8.2, C1_9.2, C1_10.2, C1_11.2, C1_12.2, C1_13.2, C1_14.2, C1_15.2, C1_16.2, C1_17.2, C1_18.2, C2_1.2, C2_2.2, C2_3.2, C3_1.2, C3_2.2, C3_3.2, C5_1.1, C5_2.1, C5_3.1, C5_4.1, C5_5.1, C5_6.1, C5_7.1, C5_8.1, C5_9.1, CD_1.2, CD_2.2, CF1.2, CFT1.2, CFT2.2, CFT3.2, CFT4.2, D1.1 (K), D2.1 (K), D3.1 (K), FL1.4, IC1.4 (PGND_1), IC1.5 (PGND_2), IC1.7 (PGND_3), IC1.8 (PGND_4), IC1.15 (MODE/SYNC), IC1.17 (SGND), IC1.21 (PGND_5), IC1.22 (PGND_6), IC1.23 (PGND_7), IC1.24 (PGND_8), IC2.4 (PGND_1), IC2.5 (PGND_2), IC2.7 (PGND_3), IC2.8 (PGND_4), IC2.15 (MODE/SYNC), IC2.17 (SGND), IC2.21 (PGND_5), IC2.22 (PGND_6), IC2.23 (PGND_7), IC2.24 (PGND_8), IC3.4 (PGND_1), IC3.5 (PGND_2), IC3.7 (PGND_3), IC3.8 (PGND_4), IC3.15 (MODE/SYNC), IC3.17 (SGND), IC3.21 (PGND_5), IC3.22 (PGND_6), IC3.23 (PGND_7), IC3.24 (PGND_8), J1.1, J2.1, J3.1, J5.8, J5.15, R2_1.2, R2_2.2, R2_3.2, R4_1.2, R4_2.2, R4_3.2, R5_1.2, R5_2.2, R5_3.2, R6_1.2, R6_2.2, R6_3.2, TP4.1 (1_1), U1.3, U2.3, U3.3, U4.1 (GND), U4.7 (GND)
GNDREXUS: FL1.3, J4.8, J4.15
unnamed: CF1.1, FL1.2, LF1.1
unnamed: D1.2 (A), RLED_1.2
unnamed: D2.2 (A), RLED_2.2
unnamed: D3.2 (A), RLED_3.2
unnamed: C4_1.1, IC1.1 (BST)
unnamed: IC1.10 (EN/UVLO), R1_1.2, R2_1.1
unnamed: C3_1.1, IC1.18 (INTVCC_1), IC1.20 (INTVCC_2)
unnamed: C4_1.2, IC1.2 (LX_1)
unnamed: IC1.6 (LX_2), L1_1.1
unnamed: IC1.13 (RT), R5_1.1
unnamed: C2_1.1, IC1.14 (SS)
unnamed: IC1.16 (~RESET/TJ), R6_1.1
unnamed: C4_2.1, IC2.1 (BST)
unnamed: IC2.10 (EN/UVLO), R1_2.2, R2_2.1
unnamed: C3_2.1, IC2.18 (INTVCC_1), IC2.20 (INTVCC_2)
unnamed: C4_2.2, IC2.2 (LX_1)
unnamed: IC2.6 (LX_2), L1_2.1
unnamed: IC2.13 (RT), R5_2.1
unnamed: C2_2.1, IC2.14 (SS)
unnamed: IC2.16 (~RESET/TJ), R6_2.1
unnamed: C4_3.1, IC3.1 (BST)
unnamed: IC3.10 (EN/UVLO), R1_3.2, R2_3.1
unnamed: C3_3.1, IC3.18 (INTVCC_1), IC3.20 (INTVCC_2)
unnamed: C4_3.2, IC3.2 (LX_1)
unnamed: IC3.6 (LX_2), L1_3.1
unnamed: IC3.13 (RT), R5_3.1
unnamed: C2_3.1, IC3.14 (SS)
unnamed: IC3.16 (~RESET/TJ), R6_3.1
unnamed: RO1.2, U1.1
unnamed: RO3.2, U2.1
unnamed: RO5.2, U3.1
VIN: C1_1.1, C1_2.1, C1_3.1, C1_4.1, C1_5.1, C1_6.1, C1_7.1, C1_8.1, C1_9.1, C1_10.1, C1_11.1, C1_12.1, C1_13.1, C1_14.1, C1_15.1, C1_16.1, C1_17.1, C1_18.1, IC1.3 (IN_1), IC1.9 (IN_2), IC1.19 (EP), IC2.3 (IN_1), IC2.9 (IN_2), IC2.19 (EP), IC3.3 (IN_1), IC3.9 (IN_2), IC3.19 (EP), LF1.2, R1_1.1, R1_2.1, R1_3.1, RO1.1, RO3.1, RO5.1
VREXUS: FL1.1, J4.1, J4.9

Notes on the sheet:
Temp/Press/Hum
3.3V
Input and output connectors
Power LEDs and TPs
